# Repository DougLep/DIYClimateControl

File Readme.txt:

See DIYClimateControl.com for more information
Doug.Leppard@teralign.com

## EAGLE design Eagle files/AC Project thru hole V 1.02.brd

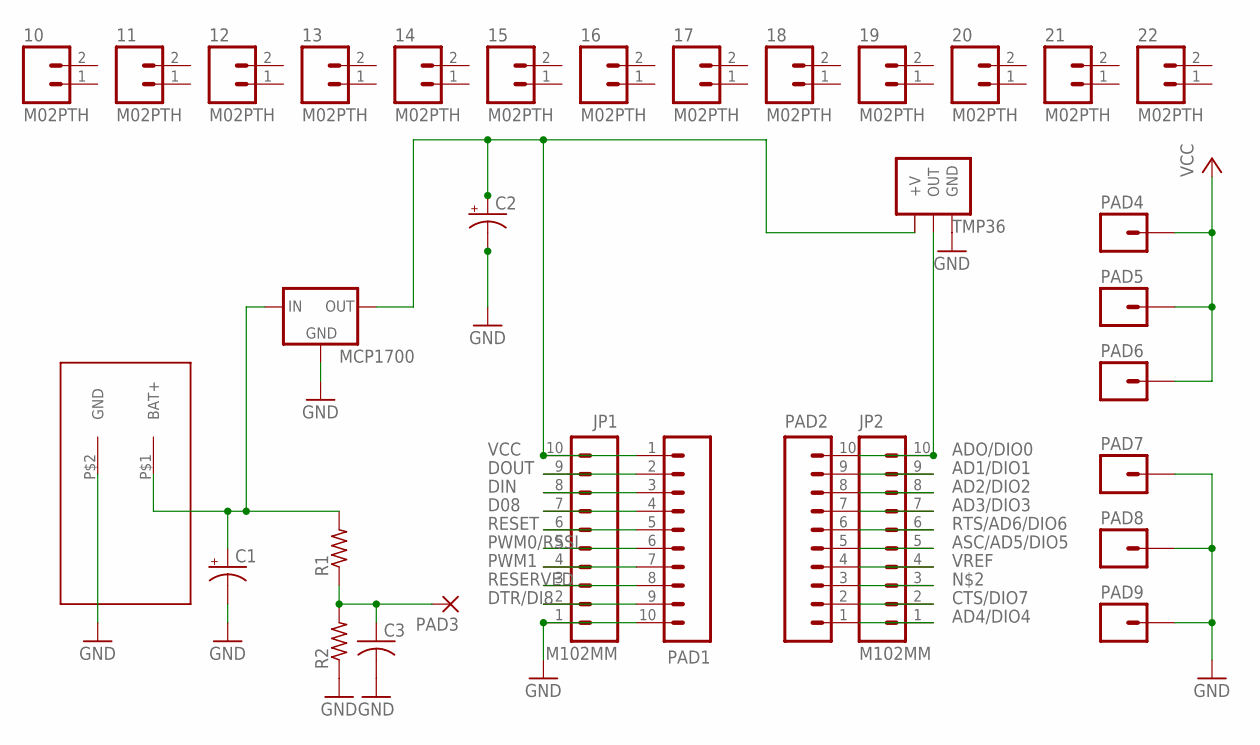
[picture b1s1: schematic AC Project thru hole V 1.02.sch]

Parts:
10, 11, 12, 13, 14, 15, 16, 17, 18, 19, 20, 21, 22: M02PTH; 1X02
C1, C2: CPOL-USE1.8-4; E1,8-4
C3: C-US050-030X075; C050-030X075
JP1, JP2: M102MM; 1X10-2MM
MCP1700: MCP1700INLINE; TO92-INLINE
PAD1, PAD2: M10"; 1X10
PAD3: 1,6/0,8
PAD4, PAD5, PAD6, PAD7, PAD8, PAD9: M01PTH; 1X01
R1, R2: R-US_0207/10; 0207/10
TMP36: TMP36INLINE; TO92-INLINE
U$2: AAA_3X_HOLDERAAA_3X_HOLDER_THROUGH_HOLE; AAA_3X_HOLDER

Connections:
AD1/DIO1: JP2.9, PAD2.9
AD2/DIO2: JP2.8, PAD2.8
AD3/DIO3: JP2.7, PAD2.7
AD4/DIO4: JP2.1, PAD2.1
ADO/DIO0: JP2.10, PAD2.10, TMP36.2 (OUT)
ASC/AD5/DIO5: JP2.5, PAD2.5
CTS/DIO7: JP2.2, PAD2.2
D08: JP1.7, PAD1.4
DIN: JP1.8, PAD1.3
DOUT: JP1.9, PAD1.2
DTR/DI8: JP1.2, PAD1.9
GND: C1.-, C2.-, C3.2, JP1.1, MCP1700.1 (GND), PAD1.10, PAD7.1, PAD8.1, PAD9.1, R2.1, TMP36.3 (GND), U$2.P$2 (GND)
unnamed: C1.+, MCP1700.2 (IN), R1.2, U$2.P$1 (BAT+)
unnamed: JP2.3, PAD2.3
unnamed: C3.1, PAD3.1, R1.1, R2.2
PWM0/RSSI: JP1.5, PAD1.6
PWM1: JP1.4, PAD1.7
RESERVED: JP1.3, PAD1.8
RESET: JP1.6, PAD1.5
RTS/AD6/DIO6: JP2.6, PAD2.6
VCC: C2.+, JP1.10, MCP1700.3 (OUT), PAD1.1, PAD4.1, PAD5.1, PAD6.1, TMP36.1 (+V)
VREF: JP2.4, PAD2.4

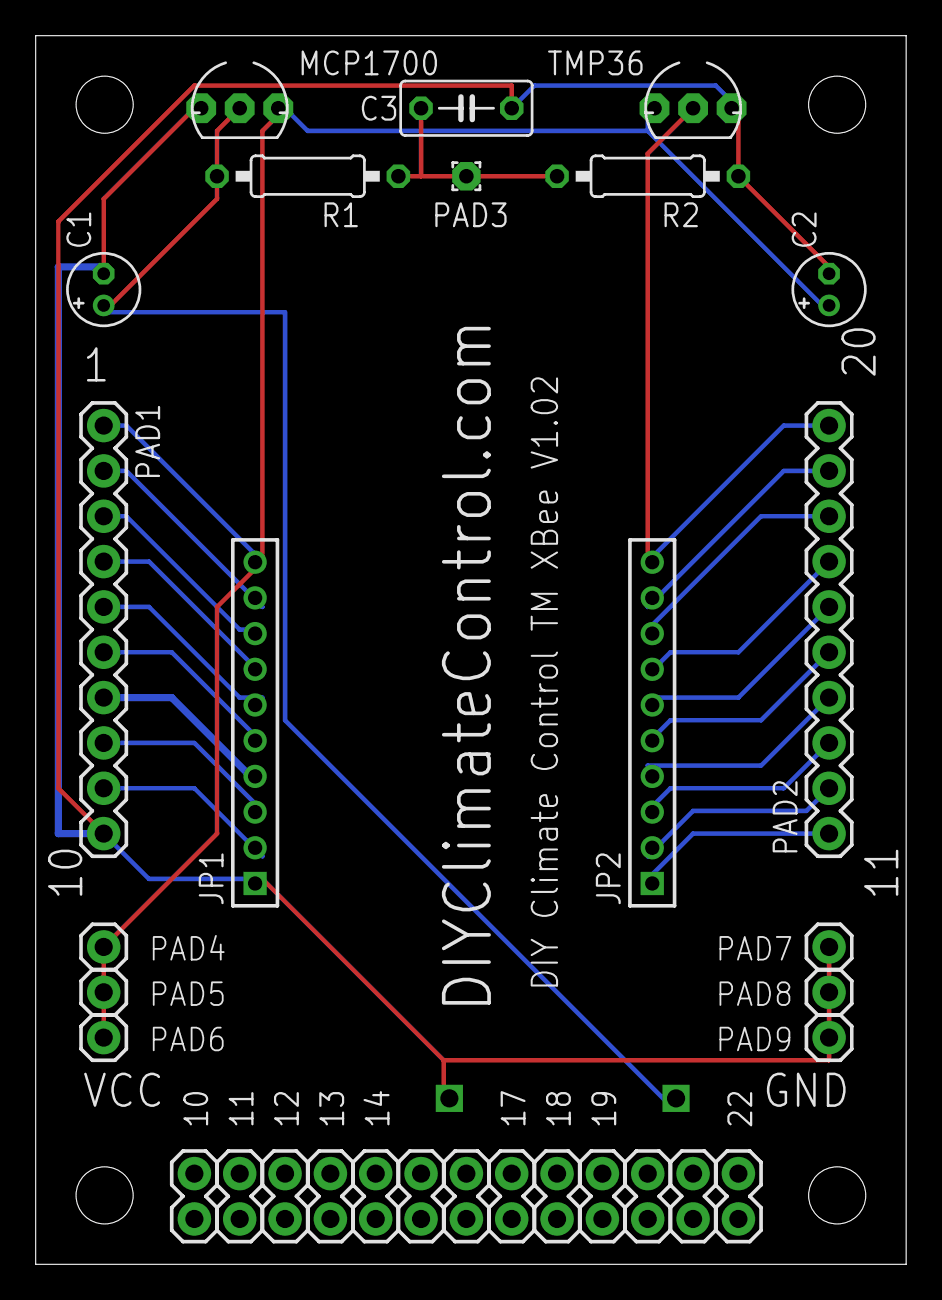
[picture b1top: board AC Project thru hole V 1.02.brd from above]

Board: 2 copper layers, 48.8 x 68.8 mm, 32 parts (1 on the bottom side), 22 nets.

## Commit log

2014-05-09 Initial Commit.
2014-07-21 First Project Commit
2014-09-05 Spark Base Added

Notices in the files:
parts and their libraries:
sparkfunconnector: Licensing: Creative Commons ShareAlike 4.0 International - https://creativecommons.org/licenses/by-sa/4.0
